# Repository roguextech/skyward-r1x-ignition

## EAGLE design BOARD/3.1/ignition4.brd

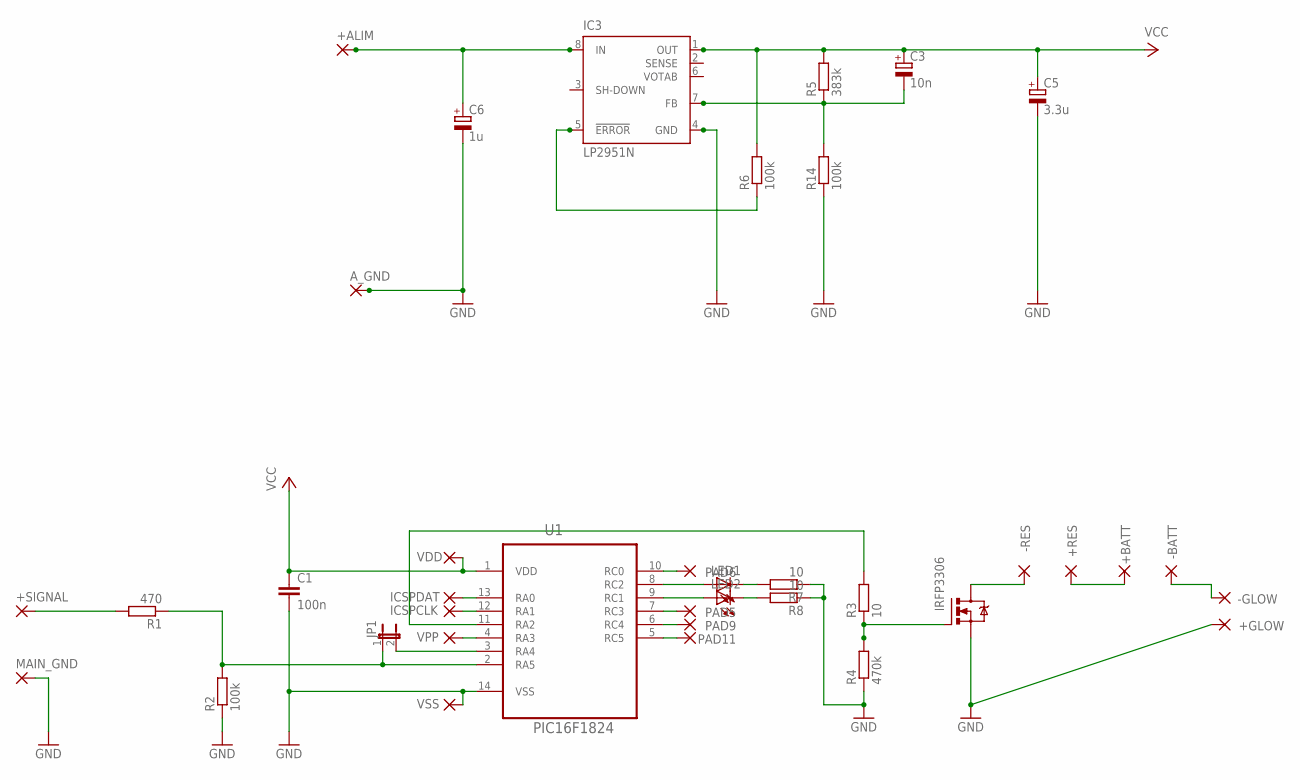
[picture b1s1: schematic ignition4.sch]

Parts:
+ALIM: 2,15/1,0
+BATT: WIREPAD3,17/1,3; 3,17/1,3
+GLOW: WIREPAD3,17/1,3; 3,17/1,3
+RES: WIREPAD3,17/1,3; 3,17/1,3
+SIGNAL: 2,15/1,0
-BATT: WIREPAD3,17/1,3; 3,17/1,3
-GLOW: WIREPAD3,17/1,3; 3,17/1,3
-RES: WIREPAD3,17/1,3; 3,17/1,3
A_GND: 2,15/1,0
C1: 100n; C050-035X075
C3: 10n; E5-6
C5: 3.3u; E2,5-5
C6: 1u; E2,5-5
IC3: LP2951N; DIL08
ICSPCLK: 2,15/1,0
ICSPDAT: 2,15/1,0
JP1: JP1E; JP1
LED1, LED2: LED3MM
MAIN_GND: 2,15/1,0
PAD5, PAD6, PAD9, PAD11: 2,15/1,0
Q2: IRFP3306; TO247BV
R1: 470; 0207/7
R2, R6, R14: 100k; 0207/7
R3, R7, R8: 10; 0207/7
R4: 470k; 0207/7
R5: 383k; 0207/7
U1: PIC16F1824; DIP254P762X533-14
VDD: WIREPAD2,15/1,0; 2,15/1,0
VPP: 2,15/1,0
VSS: WIREPAD2,15/1,0; 2,15/1,0

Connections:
GND: +GLOW.1, A_GND.1, C1.2, C5.-, C6.-, IC3.4 (GND), MAIN_GND.1, Q2.S, R2.1, R4.1, R7.1, R8.1, R14.1, U1.14 (VSS), VSS.1
unnamed: +SIGNAL.1, R1.2
unnamed: JP1.1, R1.1, R2.2, U1.2 (RA5)
unnamed: R3.2, U1.11 (RA2)
unnamed: LED1.A, U1.8 (RC2)
unnamed: +ALIM.1, C6.+, IC3.8 (IN)
unnamed: Q2.G, R3.1, R4.2
unnamed: -RES.1, Q2.D
unnamed: IC3.5 (!ERROR), R6.1
unnamed: JP1.2, U1.3 (RA4)
unnamed: +BATT.1, +RES.1
unnamed: -BATT.1, -GLOW.1
unnamed: U1.4 (RA3), VPP.1
unnamed: C3.-, IC3.7 (FB), R5.1, R14.2
unnamed: ICSPCLK.1, U1.12 (RA1)
unnamed: ICSPDAT.1, U1.13 (RA0)
unnamed: PAD6.1, U1.10 (RC0)
unnamed: LED2.A, U1.9 (RC1)
unnamed: LED1.K (C), R7.2
unnamed: PAD5.1, U1.7 (RC3)
unnamed: PAD9.1, U1.6 (RC4)
unnamed: PAD11.1, U1.5 (RC5)
unnamed: LED2.K (C), R8.2
VCC: C1.1, C3.+, C5.+, IC3.1 (OUT), R5.2, R6.2, U1.1 (VDD), VDD.1

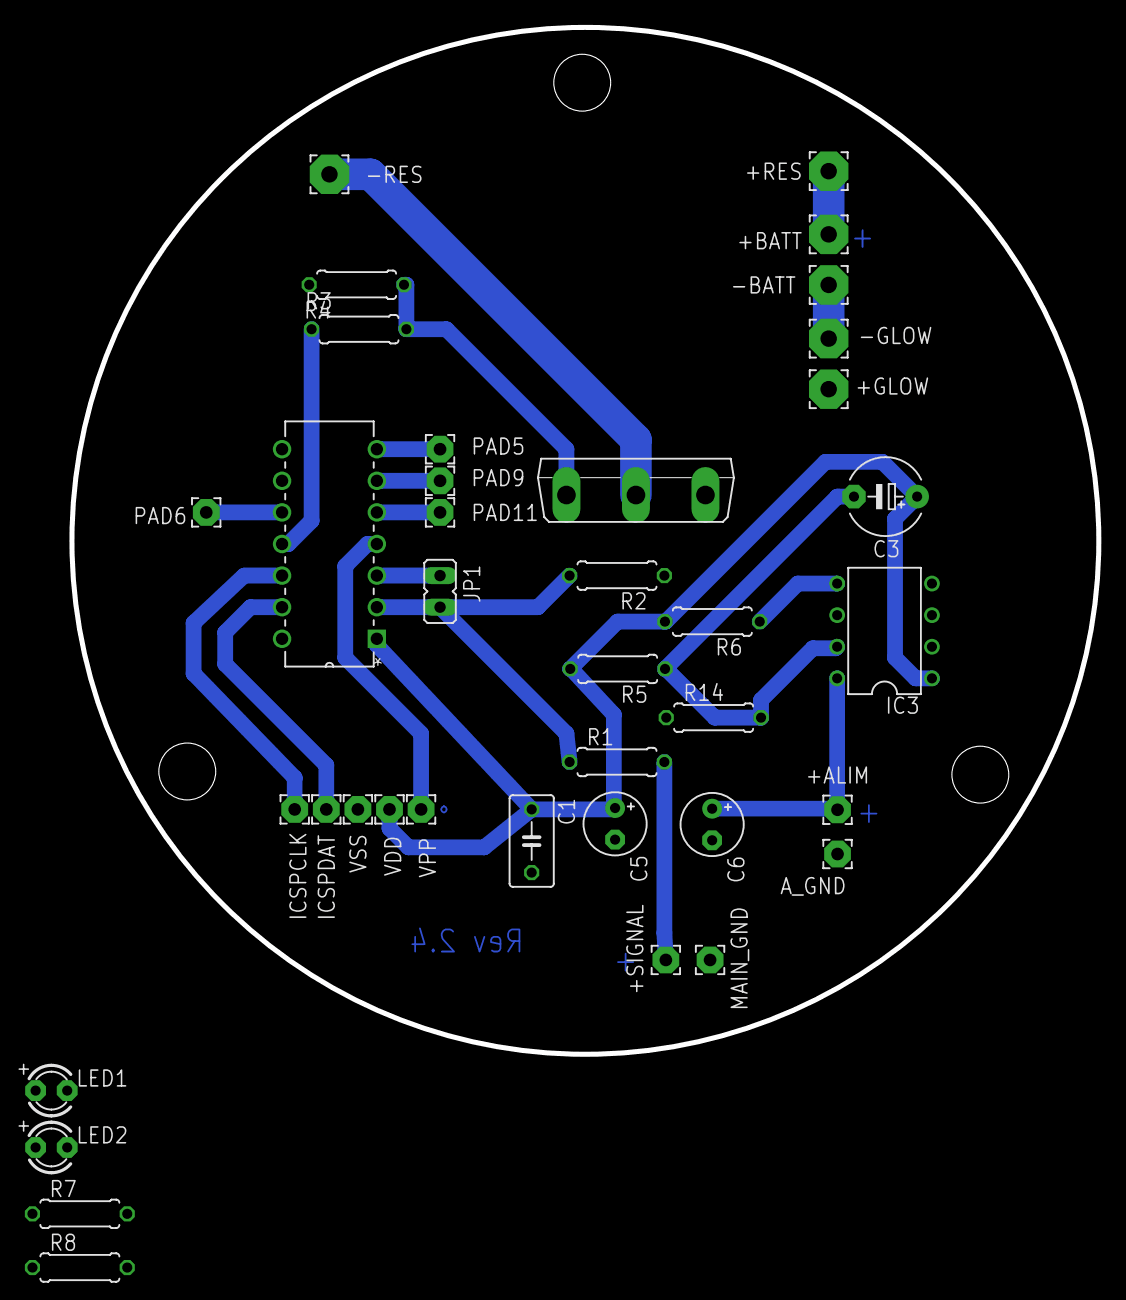
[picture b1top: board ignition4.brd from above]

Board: 4 copper layers, 82.6 x 82.6 mm, 38 parts (0 on the bottom side), 24 nets.
